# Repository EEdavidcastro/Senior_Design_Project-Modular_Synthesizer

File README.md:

# EE485-Senior Design Project-Modular_Synth
This is the Senior Design project done by David Castro and Eric Burgess at CSUF in the fall semester of 2021 (August 2021 - December 2021) on building an Analog Modular Synthesizer

A video of the behavior of the Modular synthesizer can be seen on partner's youtube channel - https://www.youtube.com/watch?v=jhq_Q-R4t1U

The report, presentation, and virtual poster for a summary of the probject are also posted on this repository:
- Video (Partner's Youtube Channel): https://www.youtube.com/watch?v=jhq_Q-R4t1U
- Report: https://github.com/EEdavidcastro/EE485-SeniorDesign-Modular_Synth/blob/main/485Final%20Report_DavidCastro_EricBurgess.pdf
- Presentation: https://github.com/EEdavidcastro/EE485-SeniorDesign-Modular_Synth/blob/main/485Final%20Presentation_DavidCastro_EricBurgess.pdf
- Virtual Poster: https://github.com/EEdavidcastro/EE485-SeniorDesign-Modular_Synth/blob/main/485Final%20Project%20Poster%20Outline_David%20Castro%26EricBurgess.pdf

Note about uploaded files in the circuit design:
  - KiCad files for pcb design
  - .ms14 files are CAD files done in multisim software to show simulation of a small portion of the circuit (important part)

Note about MIDI Design: <br>
 - The current MIDI instrument is a modified version of Elkayem’s midi2cv design done by a youtuber named
“Benny Bones.” The MIDI gerber files and code to run the MIDI is provided in this respository for ease. **The MIDI was not designed by us due to time contraints.**

Note on file labeling mistake:
- Current Source file has files inside named VCF, ignore the title/label of it being VCF, they are the current source files

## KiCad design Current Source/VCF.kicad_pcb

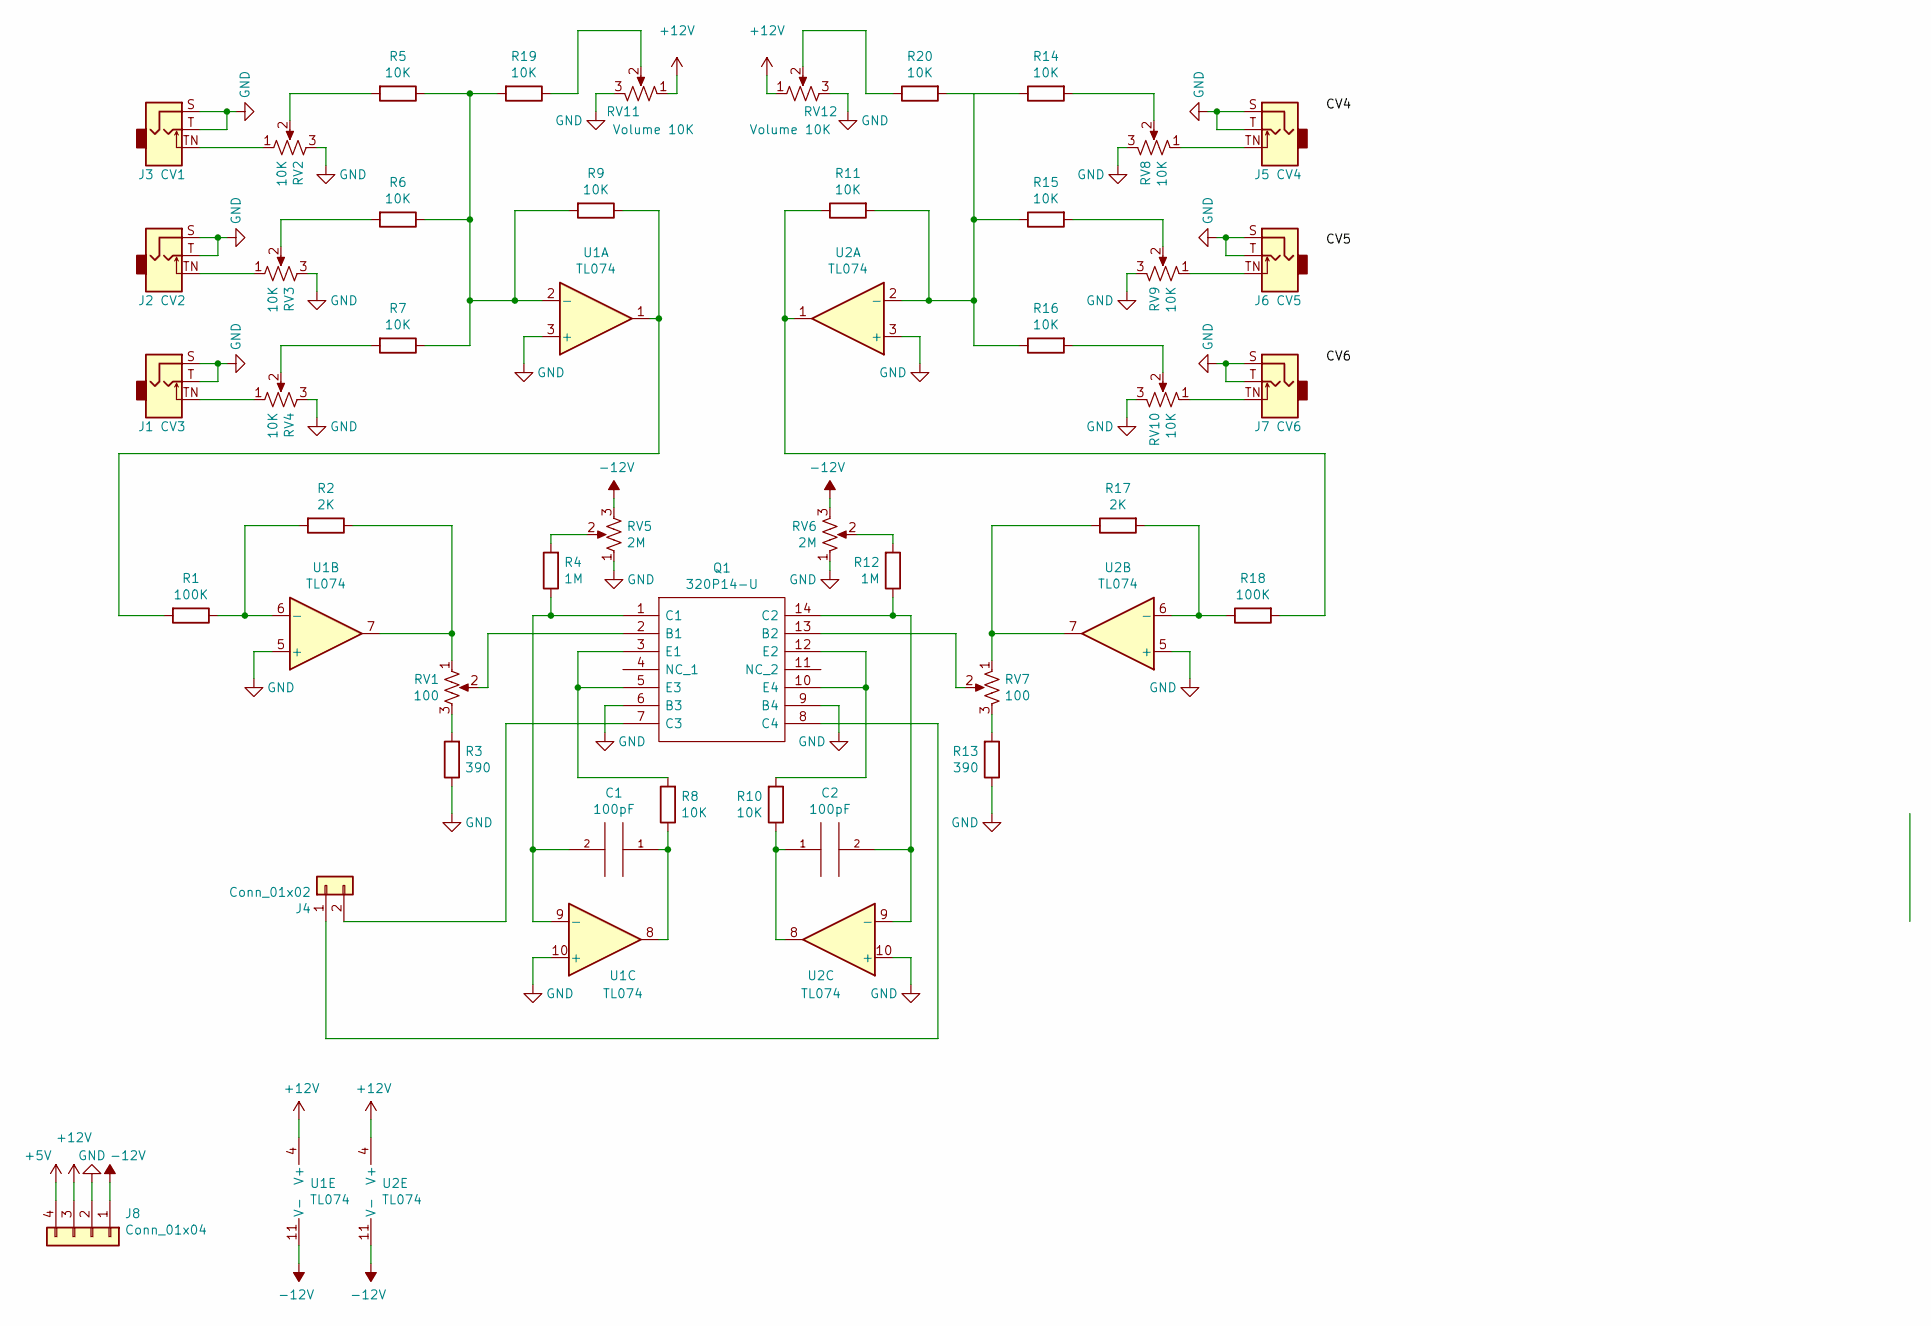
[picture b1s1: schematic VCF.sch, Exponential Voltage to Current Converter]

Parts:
C1, C2: 100pF; C_Disc_D3.8mm_W2.6mm_P2.50mm
J1: CV3; Thonkiconn_Audio_Jack_PJ398SM_W7.0mm_H2.5mm
J2: CV2; Thonkiconn_Audio_Jack_PJ398SM_W7.0mm_H2.5mm
J3: CV1; Thonkiconn_Audio_Jack_PJ398SM_W7.0mm_H2.5mm
J4: Conn_01x02; PinHeader_1x02_P2.54mm_Vertical
J5: CV4; Thonkiconn_Audio_Jack_PJ398SM_W7.0mm_H2.5mm
J6: CV5; Thonkiconn_Audio_Jack_PJ398SM_W7.0mm_H2.5mm
J7: CV6; Thonkiconn_Audio_Jack_PJ398SM_W7.0mm_H2.5mm
J8: Conn_01x04; PinHeader_1x04_P2.54mm_Vertical
Q1: 320P14-U; DIP-14_W7.62mm_Socket_LongPads; Manufacturer_Part_Number 320P14-U; Mouser Part Number 887-320P14-U
R1, R18: 100K; R_Axial_DIN0207_L6.3mm_D2.5mm_P7.62mm_Horizontal
R2, R17: 2K; R_Axial_DIN0207_L6.3mm_D2.5mm_P7.62mm_Horizontal
R3, R13: 390; R_Axial_DIN0207_L6.3mm_D2.5mm_P7.62mm_Horizontal
R4, R12: 1M; R_Axial_DIN0207_L6.3mm_D2.5mm_P7.62mm_Horizontal
R5, R6, R7, R8, R9, R10, R11, R14, R15, R16, R19, R20: 10K; R_Axial_DIN0207_L6.3mm_D2.5mm_P7.62mm_Horizontal
RV1, RV7: 100; Pot_Small_Mounting_W7.0mm_H2.5mm
RV2, RV3, RV4, RV8, RV9, RV10: 10K; Pot_Small_Mounting_W7.0mm_H2.5mm
RV5, RV6: 2M; Pot_Small_Mounting_W7.0mm_H2.5mm
RV11, RV12: Volume 10K; Pot_Small_Mounting_W7.0mm_H2.5mm
U1, U2: TL074; DIP-14_W7.62mm_Socket_LongPads

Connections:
+5V: J8.4
+12V: J8.3, RV11.1, RV12.1, U1.4 (V+), U2.4 (V+)
-12V: J8.1, RV5.3, RV6.3, U1.11 (V-), U2.11 (V-)
GND: J1.S, J1.T, J2.S, J2.T, J3.S, J3.T, J5.S, J5.T, J6.S, J6.T, J7.S, J7.T, J8.2, Q1.6 (B3), Q1.9 (B4), R3.1, R13.1, RV2.3, RV3.3, RV4.3, RV5.1, RV6.1, RV8.3, RV9.3, RV10.3, RV11.3, RV12.3, U1.3 (+), U1.5 (+), U1.10 (+), U2.3 (+), U2.5 (+), U2.10 (+)
unnamed: C1.1, R8.1, U1.8
unnamed: C1.2, Q1.1 (C1), R4.1, U1.9 (-)
unnamed: C2.1, R10.1, U2.8
unnamed: C2.2, Q1.14 (C2), R12.1, U2.9 (-)
unnamed: J1.TN, RV4.1
unnamed: J2.TN, RV3.1
unnamed: J3.TN, RV2.1
unnamed: J4.1, Q1.8 (C4)
unnamed: J4.2, Q1.7 (C3)
unnamed: J5.TN, RV8.1
unnamed: J6.TN, RV9.1
unnamed: J7.TN, RV10.1
unnamed 16: Q1.2 (B1), RV1.2; also elsewhere on the board
unnamed: Q1.3 (E1), Q1.5 (E3), R8.2
unnamed: Q1.10 (E4), Q1.12 (E2), R10.2
unnamed: Q1.13 (B2), RV7.2
unnamed: R1.1, R2.2, U1.6 (-)
unnamed: R1.2, R9.1, U1.1
unnamed 24: R2.1, RV1.1, U1.7; also elsewhere on the board
unnamed 25: R3.2, RV1.3; also elsewhere on the board
unnamed: R4.2, RV5.2
unnamed: R5.2, RV2.2
unnamed: R6.2, RV3.2
unnamed: R7.2, RV4.2
unnamed: R11.1, R18.2, U2.1
unnamed: R11.2, R14.1, R15.1, R16.1, R20.2, U2.2 (-)
unnamed: R12.2, RV6.2
unnamed: R13.2, RV7.3
unnamed: R14.2, RV8.2
unnamed: R15.2, RV9.2
unnamed: R16.2, RV10.2
unnamed: R17.1, RV7.1, U2.7
unnamed: R17.2, R18.1, U2.6 (-)
unnamed: R19.1, RV11.2
unnamed: R5.1, R6.1, R7.1, R9.2, R19.2, U1.2 (-)
unnamed: R20.1, RV12.2

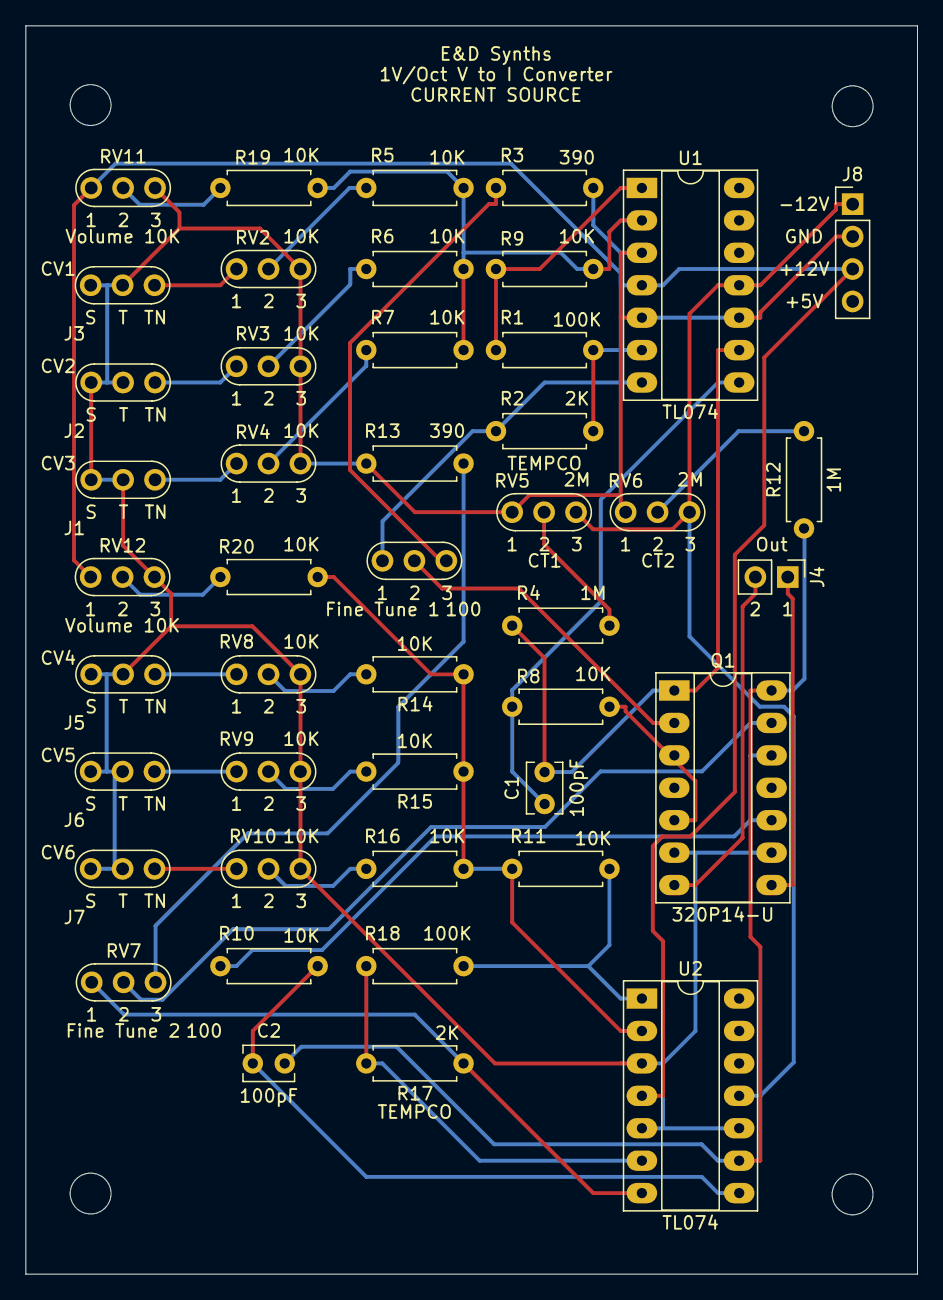
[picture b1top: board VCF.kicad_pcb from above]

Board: 2 copper layers, 69.8 x 97.8 mm, 45 parts (0 on the bottom side), 39 nets.

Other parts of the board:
Fine Tune 1: 100; Pot_Small_Mounting_W7.0mm_H2.5mm

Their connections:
unnamed 16: Fine Tune 1.2; also elsewhere on the board
unnamed 24: Fine Tune 1.1; also elsewhere on the board
unnamed 25: Fine Tune 1.3; also elsewhere on the board

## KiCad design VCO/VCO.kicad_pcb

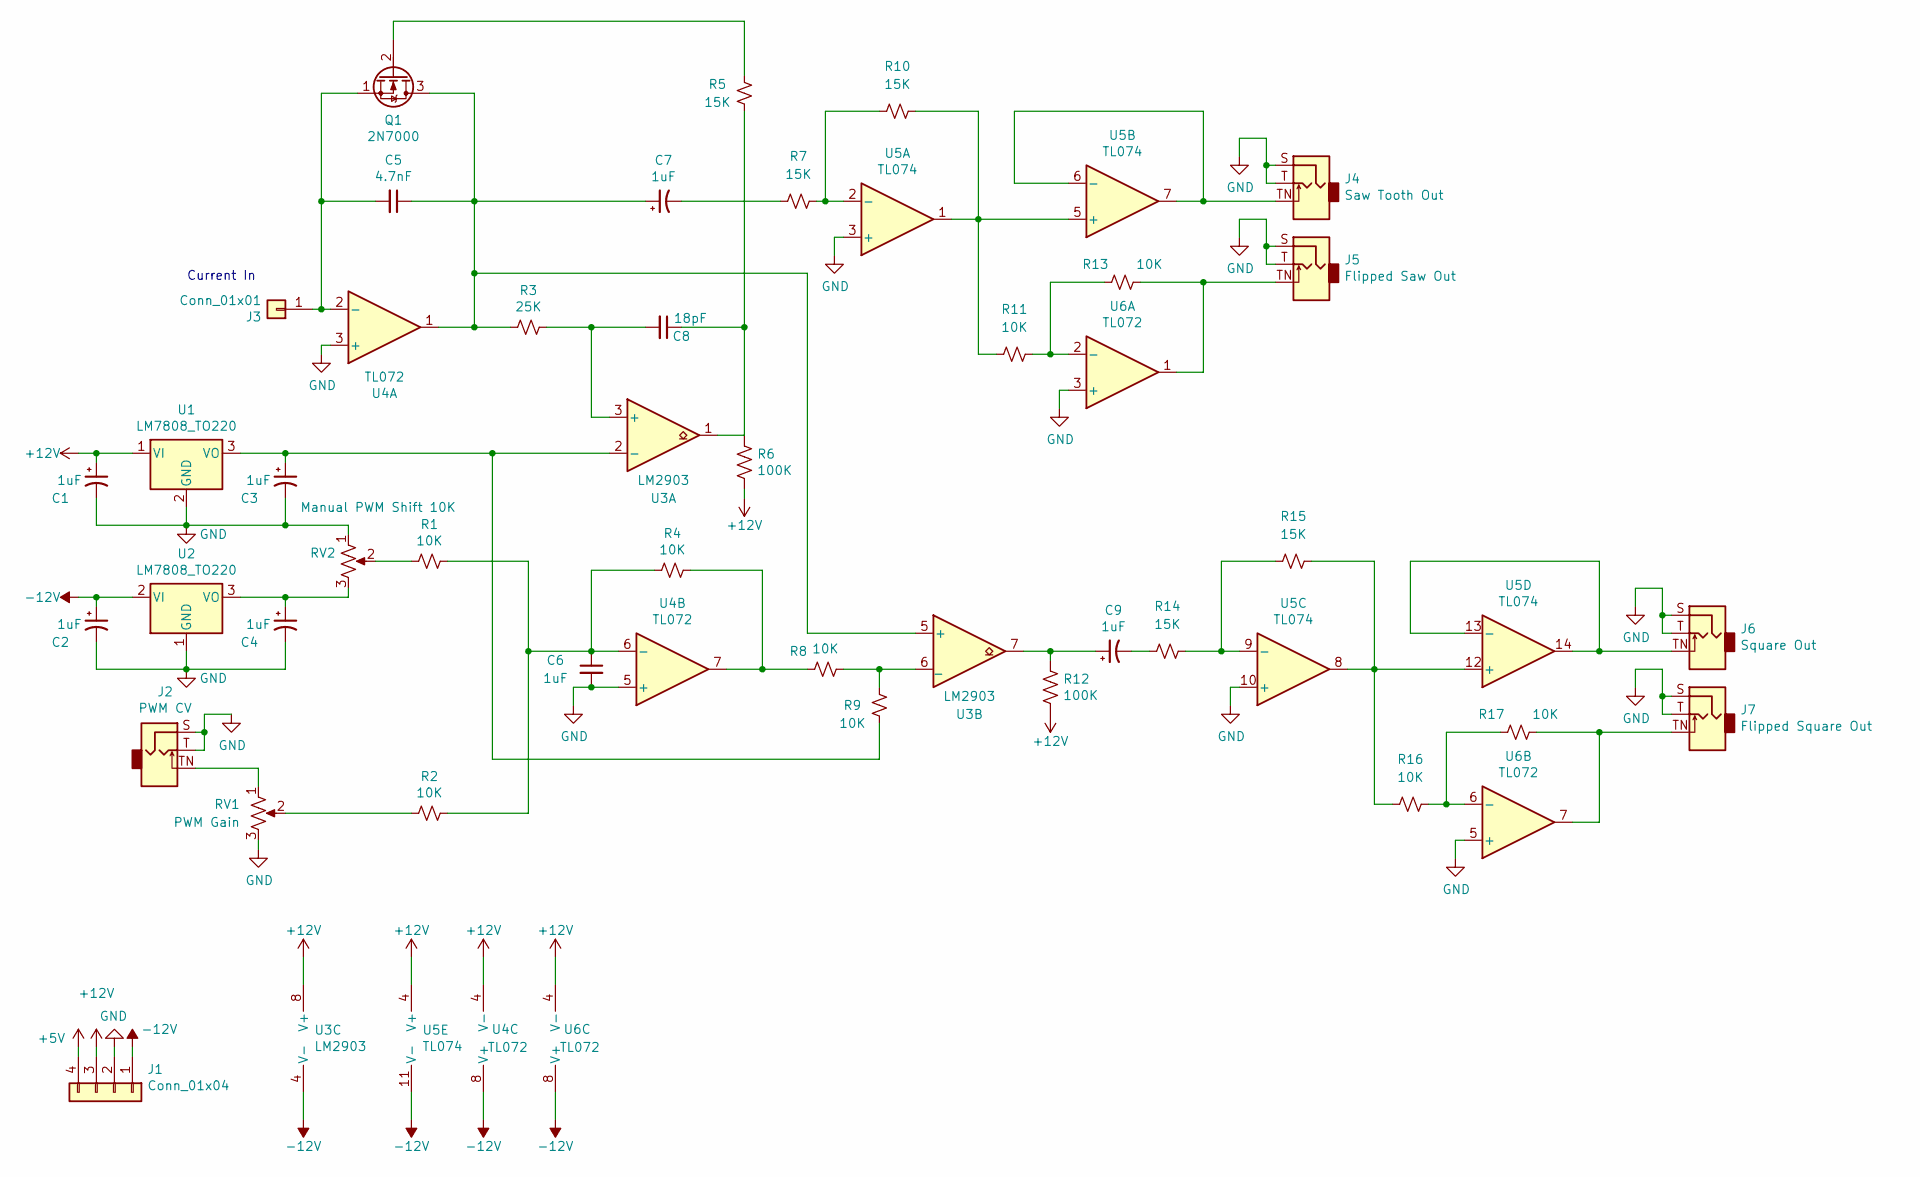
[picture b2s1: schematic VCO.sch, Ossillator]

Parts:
C1, C2, C3, C4: 1uF; CP_Radial_Tantal_D4.5mm_P2.50mm
C5: 4.7nF; C_Disc_D6.0mm_W2.5mm_P5.00mm
C6: 1uF; C_Disc_D6.0mm_W2.5mm_P5.00mm
C7, C9: 1uF; CP_Radial_D6.3mm_P2.50mm
C8: 18pF; C_Disc_D3.4mm_W2.1mm_P2.50mm
J1: Conn_01x04; PinHeader_1x04_P2.54mm_Vertical
J2: PWM CV; Thonkiconn_Audio_Jack_PJ398SM_W7.0mm_H2.5mm
J3: Conn_01x01; PinHeader_1x01_P2.54mm_Vertical
J4: Saw Tooth Out; Thonkiconn_Audio_Jack_PJ398SM_W7.0mm_H2.5mm
J5: Flipped Saw Out; Thonkiconn_Audio_Jack_PJ398SM_W7.0mm_H2.5mm
J6: Square Out; Thonkiconn_Audio_Jack_PJ398SM_W7.0mm_H2.5mm
J7: Flipped Square Out; Thonkiconn_Audio_Jack_PJ398SM_W7.0mm_H2.5mm
Q1: 2N7000; TO-92L_HandSolder
R1, R2, R4, R8, R9, R11, R13, R16, R17: 10K; R_Axial_DIN0207_L6.3mm_D2.5mm_P7.62mm_Horizontal
R3: 25K; R_Axial_DIN0207_L6.3mm_D2.5mm_P7.62mm_Horizontal
R5, R7, R10, R14, R15: 15K; R_Axial_DIN0207_L6.3mm_D2.5mm_P7.62mm_Horizontal
R6, R12: 100K; R_Axial_DIN0207_L6.3mm_D2.5mm_P7.62mm_Horizontal
RV1: PWM Gain; Pot_Small_Mounting_W7.0mm_H2.5mm
RV2: Manual PWM Shift 10K; Pot_Small_Mounting_W7.0mm_H2.5mm
U1, U2: LM7808_TO220; TO-220-3_Vertical
U3: LM2903; DIP-8_W7.62mm_Socket_LongPads
U4, U6: TL072; DIP-8_W7.62mm_Socket_LongPads
U5: TL074; DIP-14_W7.62mm_Socket_LongPads

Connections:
+5V: J1.4
+12V: C1.1, J1.3, R6.2, R12.2, U1.1 (VI), U3.8 (V+), U4.4 (V-), U5.4 (V+), U6.4 (V-)
-12V: C2.1, J1.1, U2.2 (VI), U3.4 (V-), U4.8 (V+), U5.11 (V-), U6.8 (V+)
GND: C1.2, C2.2, C3.2, C4.2, C6.2, J1.2, J2.S, J2.T, J4.S, J4.T, J5.S, J5.T, J6.S, J6.T, J7.S, J7.T, RV1.3, RV2.1, U1.2 (GND), U2.1 (GND), U4.3 (+), U4.5 (+), U5.3 (+), U5.10 (+), U6.3 (+), U6.5 (+)
unnamed: C3.1, R9.2, U1.3 (VO), U3.2 (-)
unnamed: C4.1, RV2.3, U2.3 (VO)
unnamed: C5.1, C7.1, Q1.3 (D), R3.2, U3.5 (+), U4.1
unnamed: C5.2, J3.1, Q1.1 (S), U4.2 (-)
unnamed: C6.1, R1.1, R2.1, R4.2, U4.6 (-)
unnamed: C7.2, R7.2
unnamed: C8.1, R5.2, R6.1, U3.1
unnamed: C8.2, R3.1, U3.3 (+)
unnamed: C9.1, R12.1, U3.7
unnamed: C9.2, R14.2
unnamed: J2.TN, RV1.1
unnamed: J4.TN, U5.6 (-), U5.7
unnamed: J5.TN, R13.1, U6.1
unnamed: J6.TN, U5.13 (-), U5.14
unnamed: J7.TN, R17.1, U6.7
unnamed: Q1.2 (G), R5.1
unnamed: R1.2, RV2.2
unnamed: R2.2, RV1.2
unnamed: R4.1, R8.2, U4.7
unnamed: R8.1, R9.1, U3.6 (_)
unnamed: R10.1, R11.2, U5.1, U5.5 (+)
unnamed: R7.1, R10.2, U5.2 (-)
unnamed: R11.1, R13.2, U6.2 (-)
unnamed: R14.1, R15.2, U5.9 (-)
unnamed: R15.1, R16.2, U5.8, U5.12 (+)
unnamed: R16.1, R17.2, U6.6 (-)

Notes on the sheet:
Current In

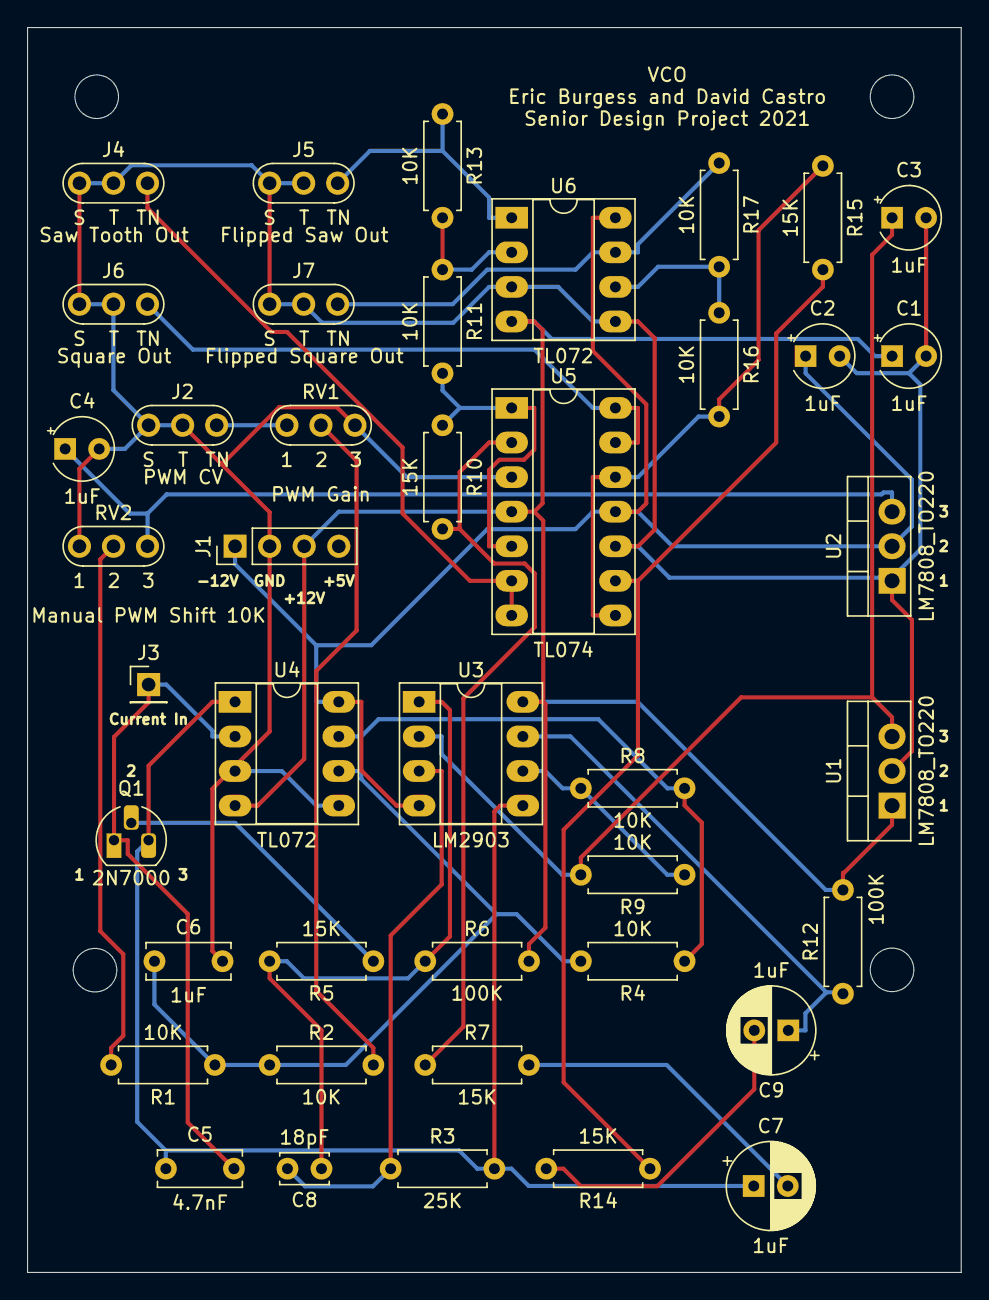
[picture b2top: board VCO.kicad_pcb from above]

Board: 2 copper layers, 68.6 x 91.4 mm, 42 parts (0 on the bottom side), 29 nets.

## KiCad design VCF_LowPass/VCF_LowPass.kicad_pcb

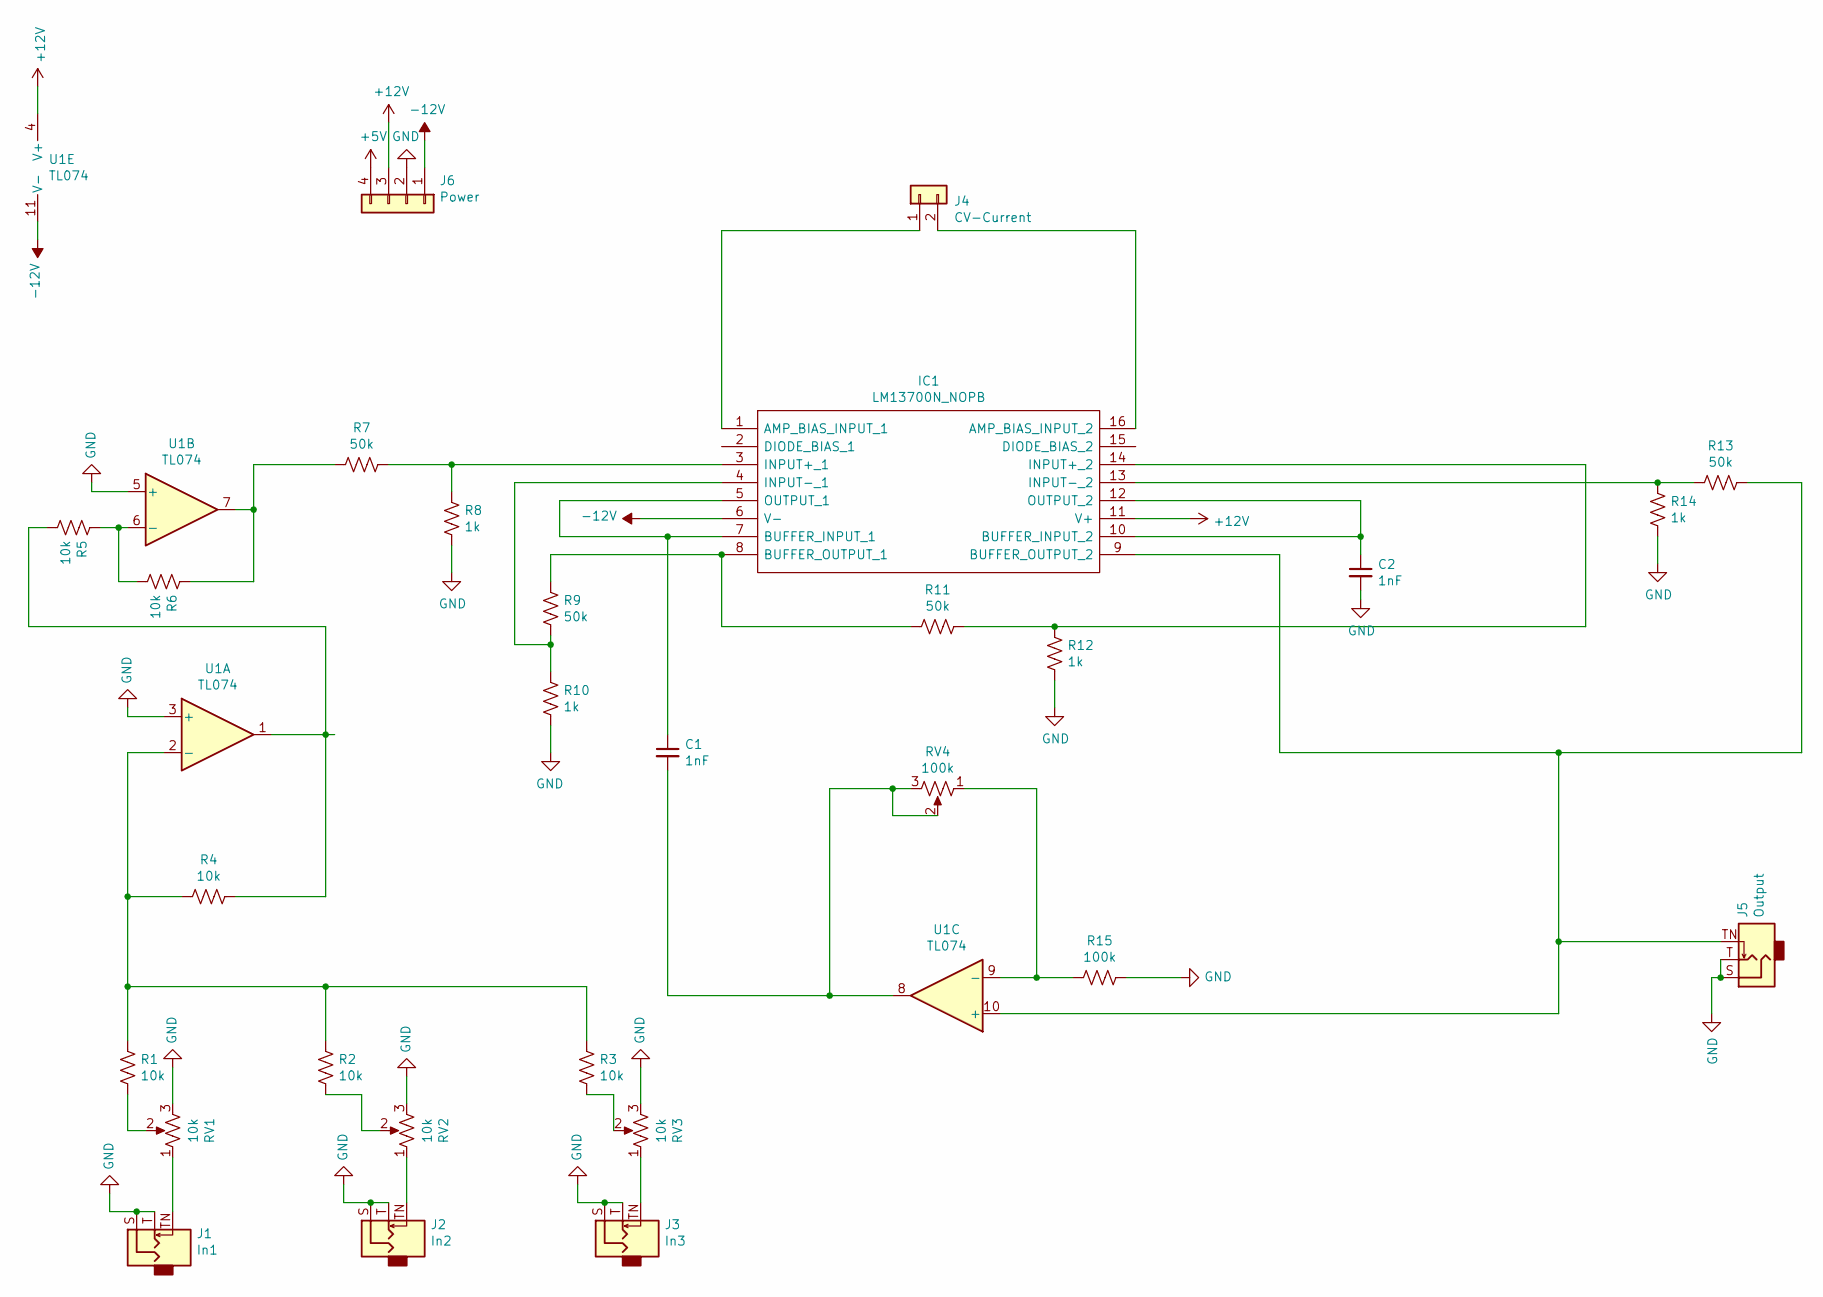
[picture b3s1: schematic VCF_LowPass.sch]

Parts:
C1: 1nF; Resonator-3Pin_W7.0mm_H2.5mm
C2: 1nF; C_Disc_D3.8mm_W2.6mm_P2.50mm
IC1: LM13700N_NOPB; DIP-16_W7.62mm_Socket_LongPads; Mouser Part Number 926-LM13700N/NOPB
J1: In1; THONK-AudioJack-PJ398SM-W3.5mm
J2: In2; THONK-AudioJack-PJ398SM-W3.5mm
J3: In3; THONK-AudioJack-PJ398SM-W3.5mm
J4: CV-Current; PinHeader_1x02_P2.54mm_Vertical
J5: Output; THONK-AudioJack-PJ398SM-W3.5mm
J6: Power; PinHeader_1x04_P2.54mm_Vertical
R1, R2, R3, R4, R5, R6: 10k; R_Axial_DIN0207_L6.3mm_D2.5mm_P7.62mm_Horizontal
R7, R9, R11, R13: 50k; R_Axial_DIN0207_L6.3mm_D2.5mm_P7.62mm_Horizontal
R8, R10, R12, R14: 1k; R_Axial_DIN0207_L6.3mm_D2.5mm_P7.62mm_Horizontal
R15: 100k; R_Axial_DIN0207_L6.3mm_D2.5mm_P7.62mm_Horizontal
RV1, RV2, RV3: 10k; POT_3_THT
RV4: 100k; POT_3_THT
U1: TL074; DIP-14_W7.62mm_Socket_LongPads

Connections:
+5V: J6.4
+12V: IC1.11 (V+), J6.3, U1.4 (V+)
-12V: IC1.6 (V-), J6.1, U1.11 (V-)
GND: C2.2, J1.S, J1.T, J2.S, J2.T, J3.S, J3.T, J5.S, J5.T, J6.2, R8.1, R10.1, R12.1, R14.1, R15.1, RV1.3, RV2.3, RV3.3, U1.3 (+), U1.5 (+)
unnamed: C1.1, IC1.5 (OUTPUT_1), IC1.7 (BUFFER_INPUT_1)
unnamed: C1.2, RV4.2, RV4.3, U1.8
unnamed: C2.1, IC1.10 (BUFFER_INPUT_2), IC1.12 (OUTPUT_2)
unnamed: IC1.1 (AMP_BIAS_INPUT_1), J4.1
unnamed: IC1.3 (INPUT+_1), R7.1, R8.2
unnamed: IC1.4 (INPUT-_1), R9.1, R10.2
unnamed: IC1.8 (BUFFER_OUTPUT_1), R9.2, R11.2
unnamed: IC1.9 (BUFFER_OUTPUT_2), J5.TN, R13.2, U1.10 (+)
unnamed: IC1.13 (INPUT-_2), R13.1, R14.2
unnamed: IC1.14 (INPUT+_2), R11.1, R12.2
unnamed: IC1.16 (AMP_BIAS_INPUT_2), J4.2
unnamed: J1.TN, RV1.1
unnamed: J2.TN, RV2.1
unnamed: J3.TN, RV3.1
unnamed: R1.1, RV1.2
unnamed: R1.2, R2.2, R3.2, R4.2, U1.2 (-)
unnamed: R2.1, RV2.2
unnamed: R3.1, RV3.2
unnamed: R4.1, R5.1, U1.1
unnamed: R5.2, R6.1, U1.6 (-)
unnamed: R6.2, R7.2, U1.7
unnamed: R15.2, RV4.1, U1.9 (-)

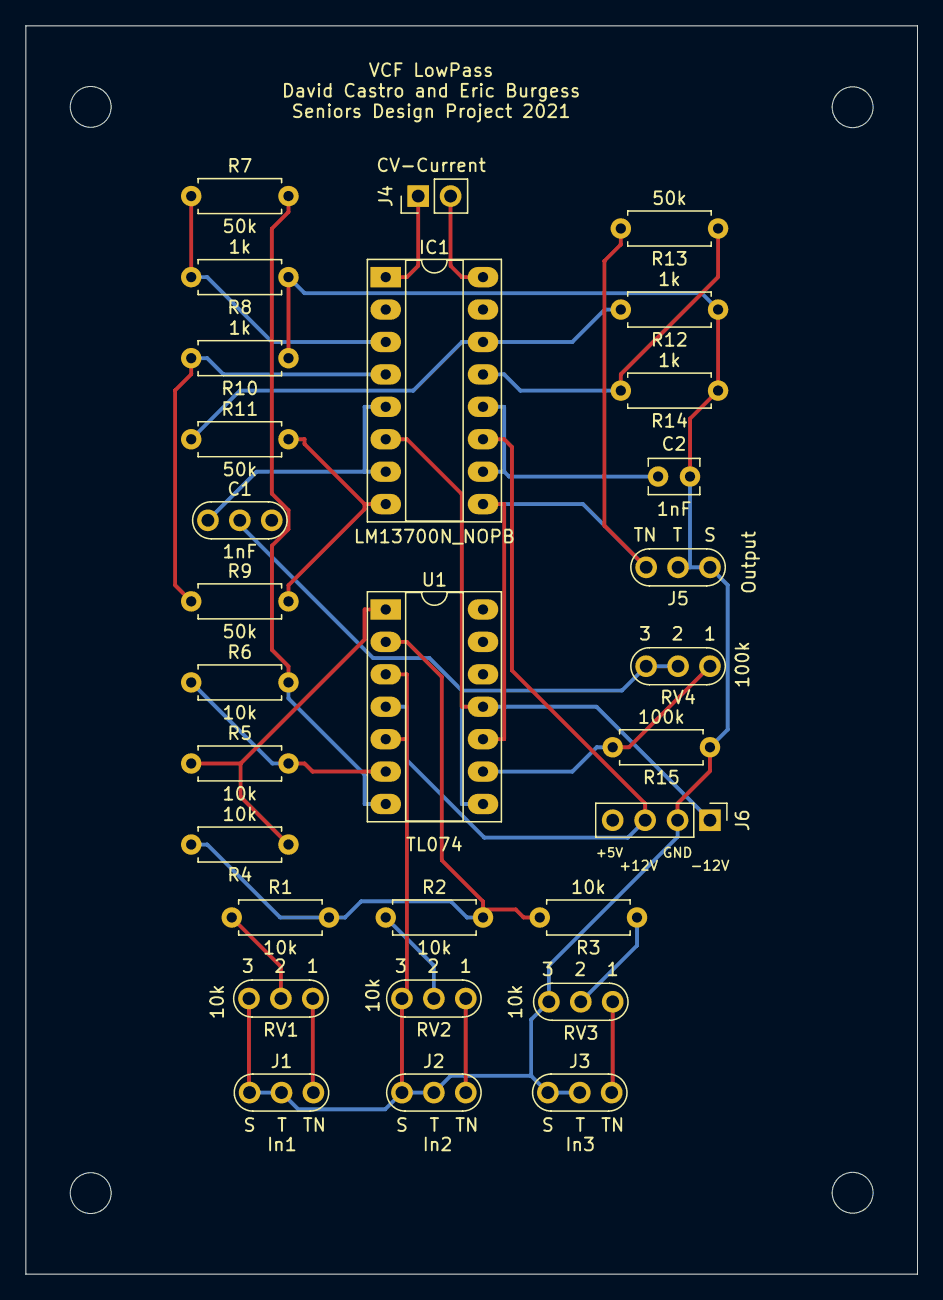
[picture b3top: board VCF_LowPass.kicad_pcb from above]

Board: 2 copper layers, 69.8 x 97.8 mm, 29 parts (0 on the bottom side), 25 nets.

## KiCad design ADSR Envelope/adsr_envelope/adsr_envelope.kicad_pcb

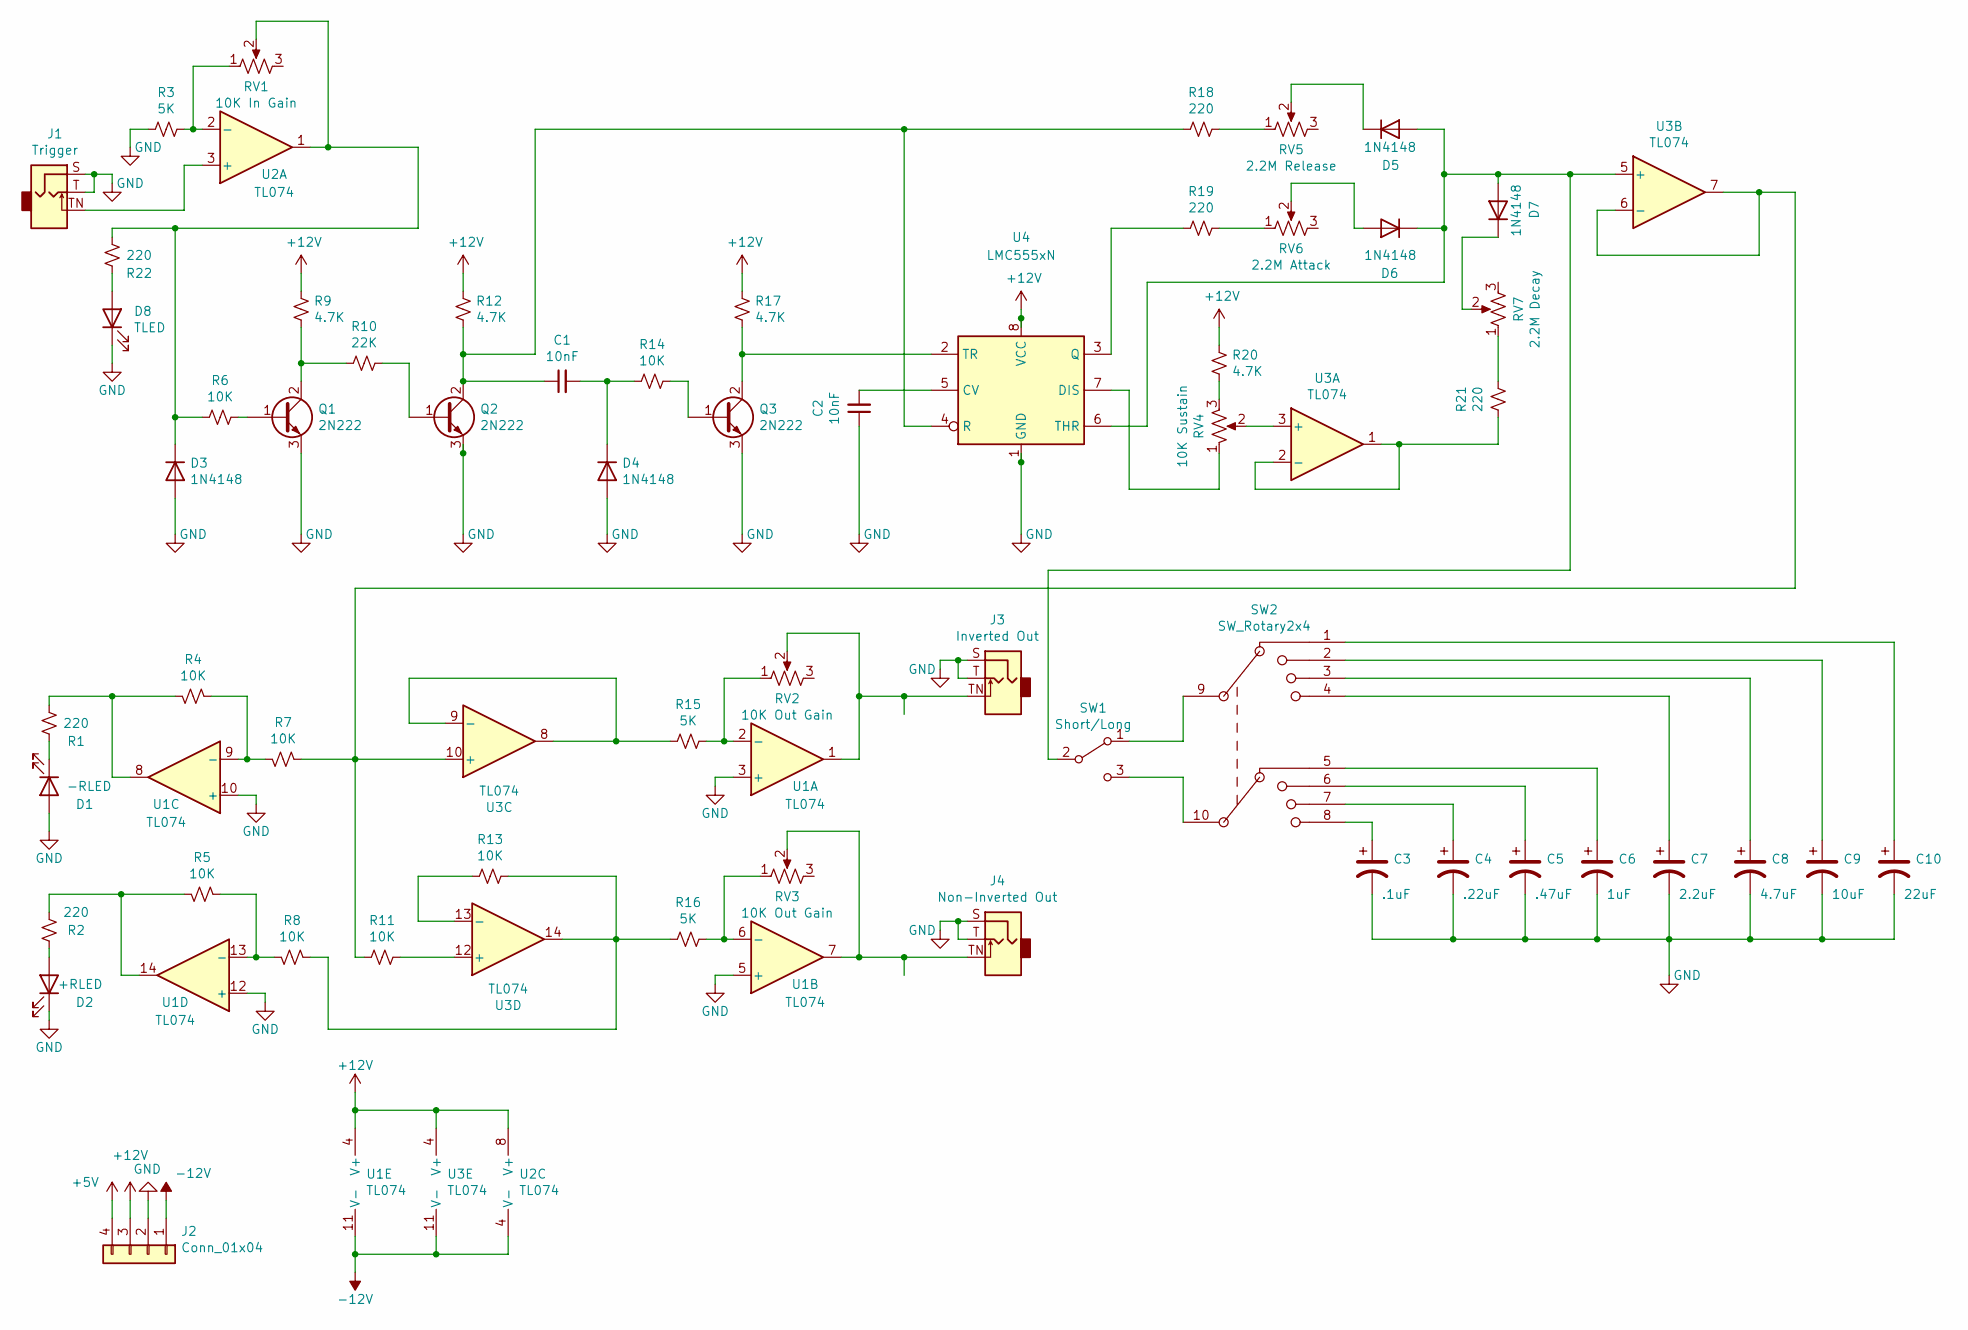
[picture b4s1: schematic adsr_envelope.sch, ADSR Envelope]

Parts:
C1, C2: 10nF; C_Disc_D6.0mm_W2.5mm_P5.00mm
C3: .1uF; CP_Radial_D6.3mm_P2.50mm
C4: .22uF; CP_Radial_D6.3mm_P2.50mm
C5: .47uF; CP_Radial_D6.3mm_P2.50mm
C6: 1uF; CP_Radial_D6.3mm_P2.50mm
C7: 2.2uF; CP_Radial_D6.3mm_P2.50mm
C8: 4.7uF; CP_Radial_D6.3mm_P2.50mm
C9: 10uF; CP_Radial_D6.3mm_P2.50mm
C10: 22uF; CP_Radial_D6.3mm_P2.50mm
D1: -RLED; LED_D3.0mm
D2: +RLED; LED_D3.0mm
D3, D4, D5, D6, D7: 1N4148; D_A-405_P7.62mm_Horizontal
D8: TLED; LED_D3.0mm
J1: Trigger; Thonkiconn_Audio_Jack_PJ398SM_W7.0mm_H2.5mm
J2: Conn_01x04; PinHeader_1x04_P2.54mm_Vertical
J3: Inverted Out; Thonkiconn_Audio_Jack_PJ398SM_W7.0mm_H2.5mm
J4: Non-Inverted Out; Thonkiconn_Audio_Jack_PJ398SM_W7.0mm_H2.5mm
Q1, Q2, Q3: 2N222; TO-92L_HandSolder
R1, R2, R18, R19, R21, R22: 220; R_Axial_DIN0207_L6.3mm_D2.5mm_P7.62mm_Horizontal
R3, R15, R16: 5K; R_Axial_DIN0207_L6.3mm_D2.5mm_P7.62mm_Horizontal
R4, R5, R6, R7, R8, R11, R13, R14: 10K; R_Axial_DIN0207_L6.3mm_D2.5mm_P7.62mm_Horizontal
R9, R12, R17, R20: 4.7K; R_Axial_DIN0207_L6.3mm_D2.5mm_P7.62mm_Horizontal
R10: 22K; R_Axial_DIN0207_L6.3mm_D2.5mm_P7.62mm_Horizontal
RV1: 10K In Gain; Pot_Small_Mounting_W7.0mm_H2.5mm
RV2, RV3: 10K Out Gain; Pot_Small_Mounting_W7.0mm_H2.5mm
RV4: 10K Sustain; Pot_Small_Mounting_W7.0mm_H2.5mm
RV5: 2.2M Release; Pot_Small_Mounting_W7.0mm_H2.5mm
RV6: 2.2M Attack; Pot_Small_Mounting_W7.0mm_H2.5mm
RV7: 2.2M Decay; Pot_Small_Mounting_W7.0mm_H2.5mm
SW1: Short/Long; PinHeader_1x03_P2.54mm_Vertical
SW2: SW_Rotary2x4; PinHeader_1x10_P2.54mm_Vertical
U1, U3: TL074; DIP-14_W7.62mm_Socket_LongPads
U2: TL074; DIP-8_W7.62mm_Socket_LongPads
U4: LMC555xN; DIP-8_W7.62mm_Socket_LongPads

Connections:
+5V: J2.4
+12V: J2.3, R9.1, R12.1, R17.1, R20.1, U1.4 (V+), U2.8 (V+), U3.4 (V+), U4.8 (VCC)
-12V: J2.1, U1.11 (V-), U2.4 (V-), U3.11 (V-)
GND: C2.1, C3.2, C4.2, C5.2, C6.2, C7.2, C8.2, C9.2, C10.2, D1.2 (A), D2.1 (K), D3.2 (A), D4.2 (A), D8.1 (K), J1.S, J1.T, J2.2, J3.S, J3.T, J4.S, J4.T, Q1.3 (E), Q2.3 (E), Q3.3 (E), R3.1, U1.3 (+), U1.5 (+), U1.10 (+), U1.12 (+), U4.1 (GND)
unnamed: C1.1, Q2.2 (C), R12.2, R18.1, U4.4 (R)
unnamed: C1.2, D4.1 (K), R14.2
unnamed: C2.2, U4.5 (CV)
unnamed: C3.1, SW2.8
unnamed: C4.1, SW2.7
unnamed: C5.1, SW2.6
unnamed: C6.1, SW2.5
unnamed: C7.1, SW2.4
unnamed: C8.1, SW2.3
unnamed: C9.1, SW2.2
unnamed: C10.1, SW2.1
unnamed: D1.1 (K), R1.2
unnamed: D2.2 (A), R2.2
unnamed: D3.1 (K), R6.2, R22.1, RV1.2, U2.1
unnamed: D5.1 (K), RV5.2
unnamed: D5.2 (A), D6.1 (K), D7.2 (A), SW1.2 (B), U3.5 (+), U4.6 (THR)
unnamed: D6.2 (A), RV6.2
unnamed: D7.1 (K), RV7.2
unnamed: D8.2 (A), R22.2
unnamed: J1.TN, U2.3 (+)
unnamed: J3.TN, RV2.2, U1.1
unnamed: J4.TN, RV3.2, U1.7
unnamed: Q1.1 (B), R6.1
unnamed: Q1.2 (C), R9.2, R10.1
unnamed: Q2.1 (B), R10.2
unnamed: Q3.1 (B), R14.1
unnamed: Q3.2 (C), R17.2, U4.2 (TR)
unnamed: R1.1, R4.2, U1.8
unnamed: R2.1, R5.2, U1.14
unnamed: R3.2, RV1.1, U2.2 (-)
unnamed: R4.1, R7.2, U1.9 (-)
unnamed: R5.1, R8.2, U1.13 (-)
unnamed: R7.1, R11.1, U3.6 (-), U3.7, U3.10 (+)
unnamed: R11.2, U3.12 (+)
unnamed: R13.1, U3.13 (-)
unnamed: R8.1, R13.2, R16.1, U3.14
unnamed: R15.1, U3.8, U3.9 (-)
unnamed: R15.2, RV2.1, U1.2 (-)
unnamed: R16.2, RV3.1, U1.6 (-)
unnamed: R18.2, RV5.1
unnamed: R19.1, U4.3 (Q)
unnamed: R19.2, RV6.1
unnamed: R20.2, RV4.3
unnamed: R21.1, U3.1, U3.2 (-)
unnamed: R21.2, RV7.1
unnamed: RV4.1, U4.7 (DIS)
unnamed: RV4.2, U3.3 (+)
unnamed: SW1.1 (A), SW2.9
unnamed: SW1.3 (C), SW2.10

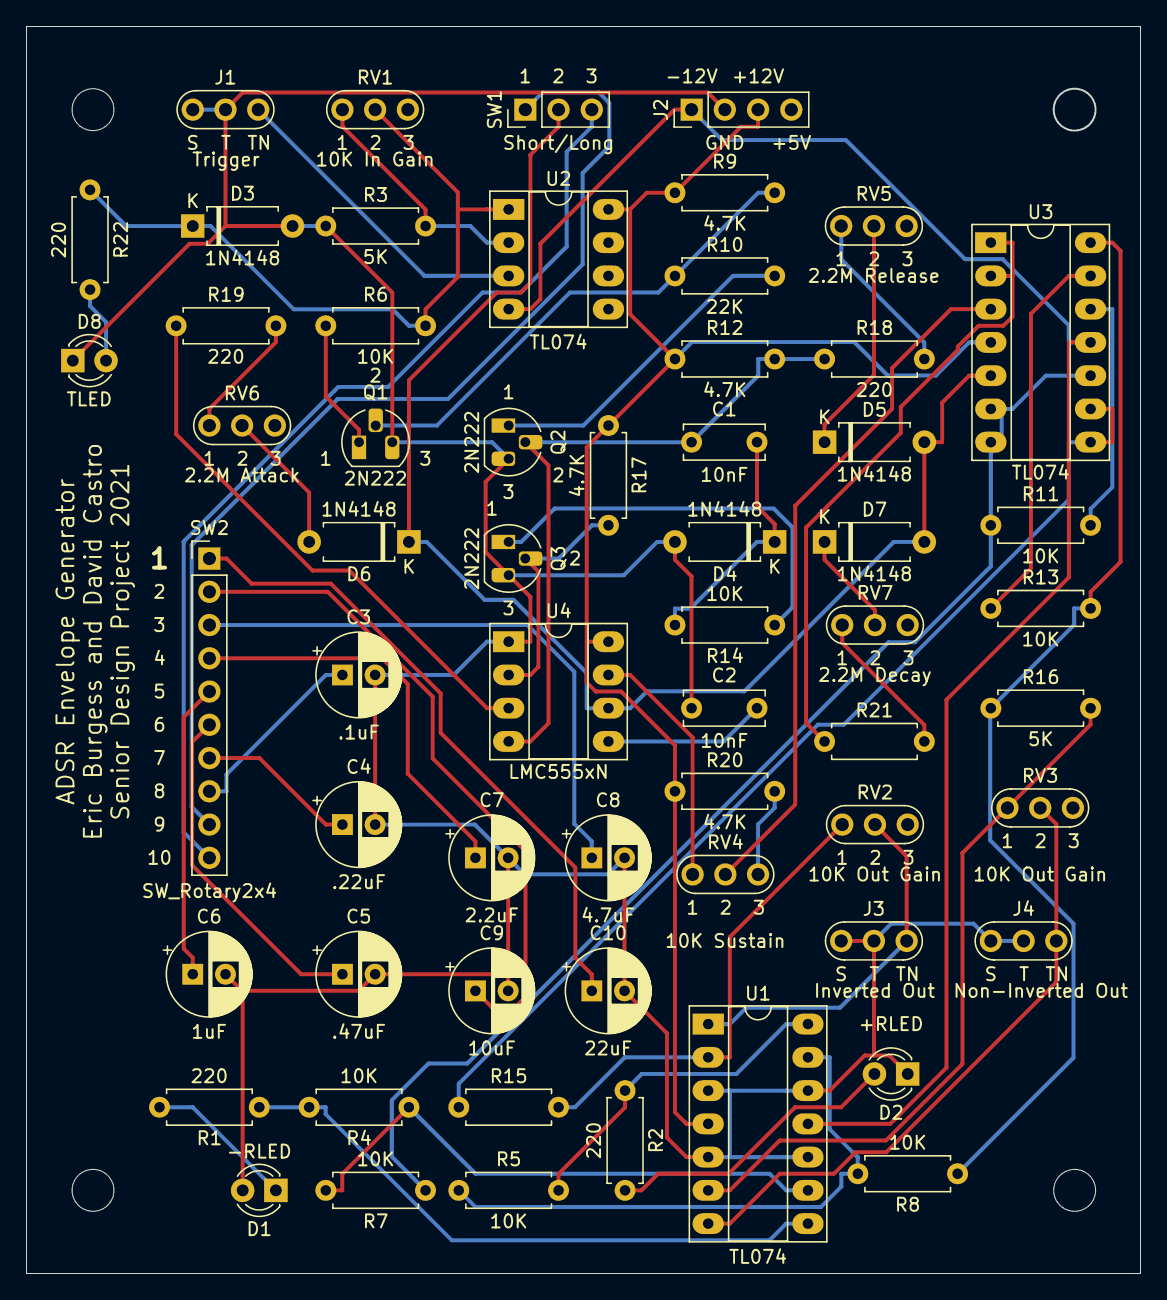
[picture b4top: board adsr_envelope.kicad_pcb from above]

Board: 2 copper layers, 85.0 x 95.2 mm, 60 parts (0 on the bottom side), 52 nets.
